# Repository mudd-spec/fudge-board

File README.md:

# fudge board
------ 
## Important!
This board charges batteries but does NOT run off batteries connected to the BAT and GND terminals. I plan to make a revised version where this is changed.

This is an RP2040 dev board created based off the <a href="https://github.com/KaiPereira/build-a-devboard">guide</a> from Blueprint at Hackclub!

### Features
- RP2040 Chip
- 12MHz Crystal Oscillator
- Many GPIO Pins
- a 1 Cell Lipo/Li-ion Battery Charger
- LED connected to GPIO
- USB-C
- 16MB of Flash Memory
- LDO Power Regulator

#### KiCad
The entire board was made with this software! The pictures below are taken from KiCad!

<strong>Schematic</strong>

<strong>PCB</strong>

#### JLCPCB
Here is a sample of what manufacturing the board might cost.

<strong>BOM</strong>

<strong>Final Price</strong>

#### Excalidraw
All silkscreen drawings were made with this handy website.
#### Extra
From this project I learned a lot more about how common communication interfaces like SPI, UART, and I2C work. I quickly picked up on electronics basics such as the theory behind decoupling capacitors, pull-up/pull-down resistors, and common electronics components (flash memory ics, crystal oscillators, etc.). I hope with this knowledge, I can continue on to put together a little single board computer, like the common Raspberry Pi.

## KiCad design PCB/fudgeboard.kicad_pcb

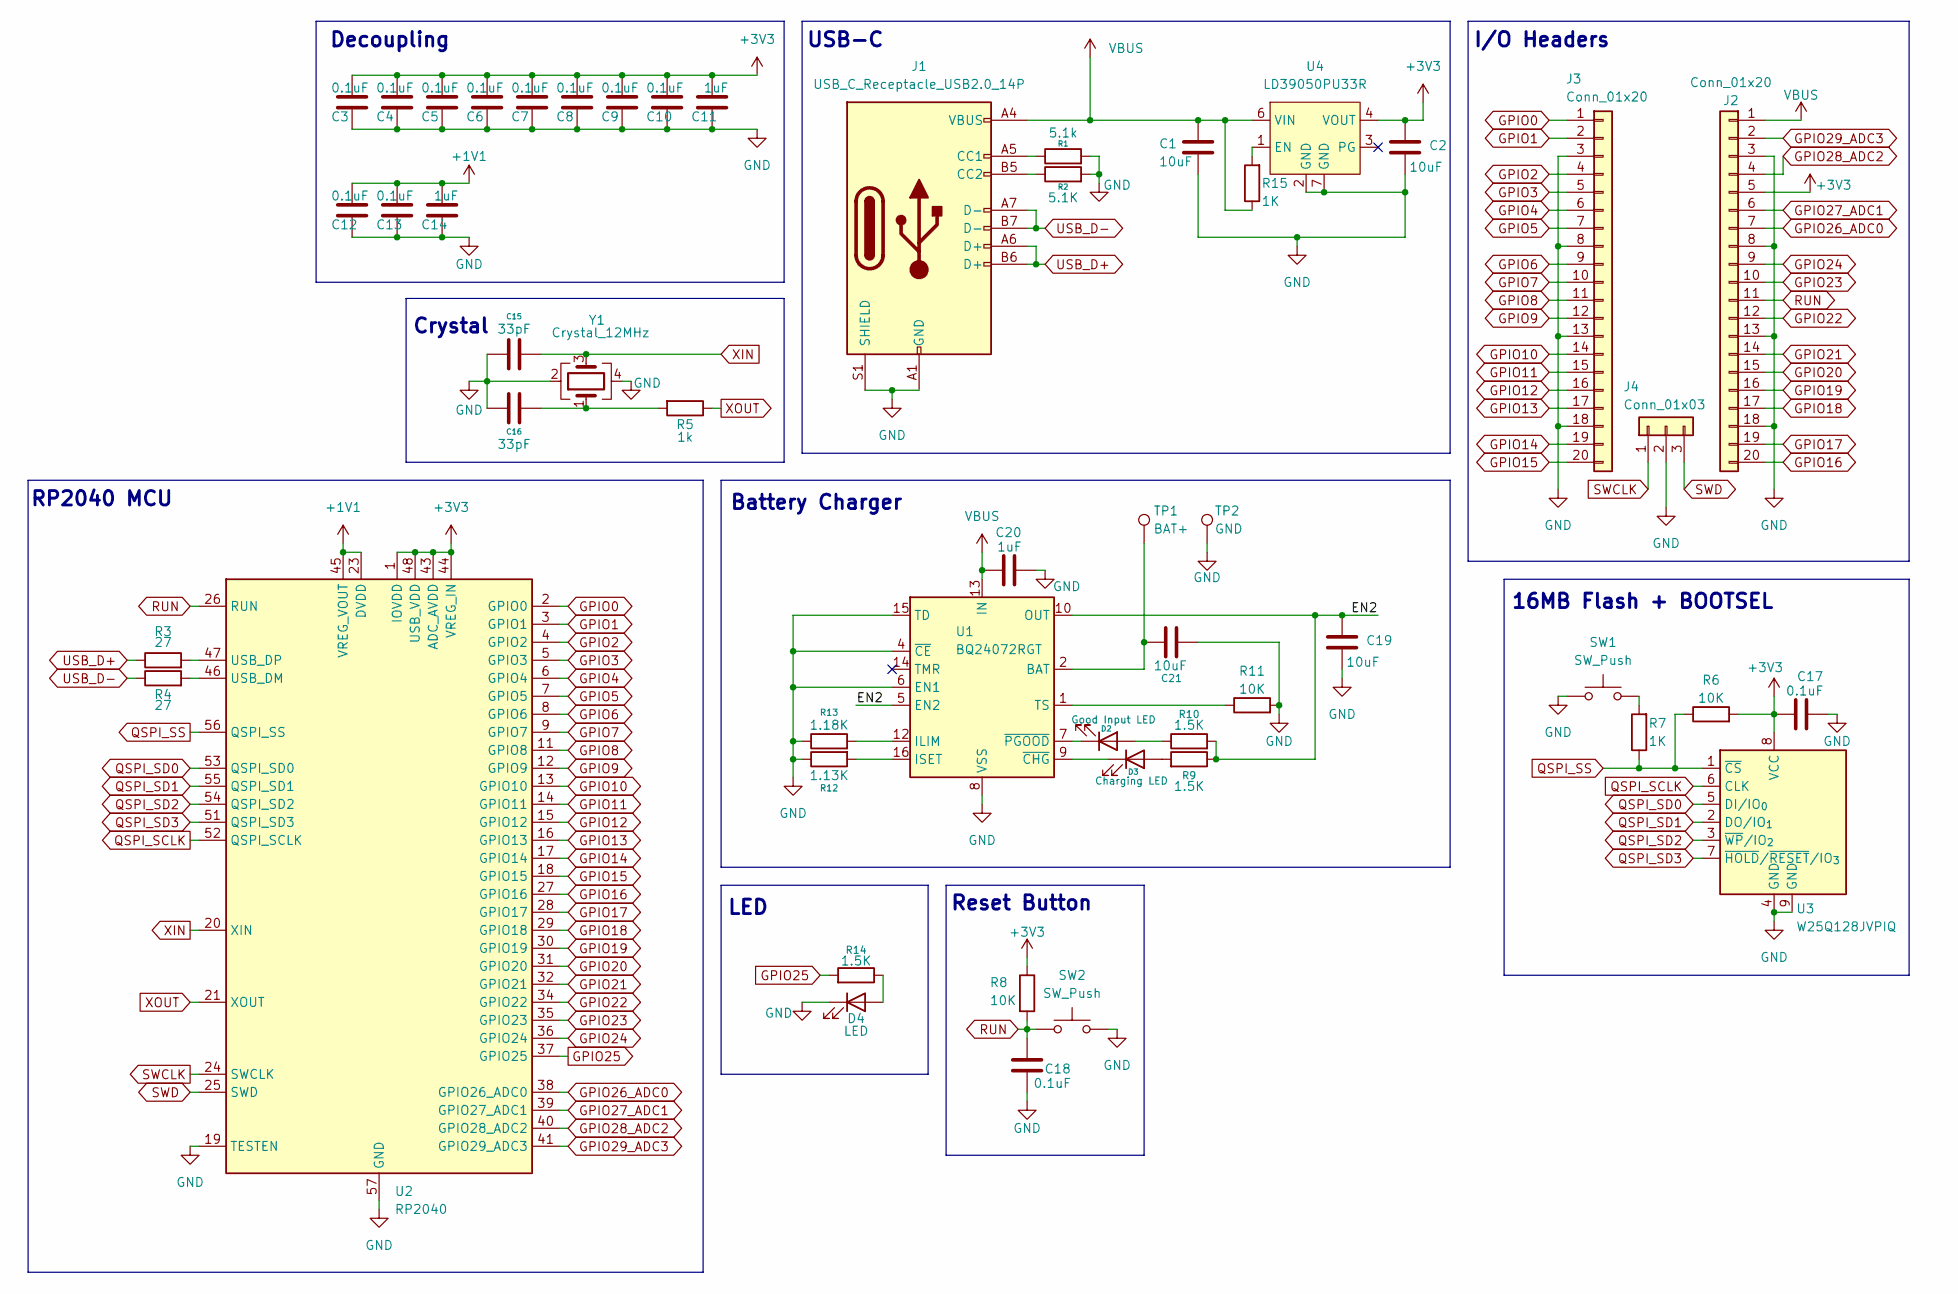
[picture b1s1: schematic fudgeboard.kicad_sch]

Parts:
C1, C2, C19, C21: 10uF; C_0603_1608Metric
C3, C4, C5, C6, C7, C8, C9, C10, C12, C13, C17, C18: 0.1uF; C_0402_1005Metric
C11, C14, C20: 1uF; C_0402_1005Metric
C15, C16: 33pF; C_0402_1005Metric
D2: Good Input LED; LED_0603_1608Metric
D3: Charging LED; LED_0603_1608Metric
D4: LED; LED_0603_1608Metric
J1: USB_C_Receptacle_USB2.0_14P; USB_C_Receptacle_HRO_TYPE-C-31-M-12
J2, J3: Conn_01x20; PinHeader_1x20_P2.54mm_Vertical
J4: Conn_01x03; PinHeader_1x03_P2.54mm_Vertical
R1: 5.1k; R_0402_1005Metric
R2: 5.1K; R_0402_1005Metric
R3, R4: 27; R_0402_1005Metric
R5: 1k; R_0402_1005Metric
R6, R8, R11: 10K; R_0402_1005Metric
R7, R15: 1K; R_0402_1005Metric
R9, R10, R14: 1.5K; R_0402_1005Metric
R12: 1.13K; R_0402_1005Metric
R13: 1.18K; R_0402_1005Metric
SW1, SW2: SW_Push; SW_Push_SPST_NO_Alps_SKRK
TP1: BAT+; TestPoint_Pad_2.5x2.5mm
TP2: GND; TestPoint_Pad_2.5x2.5mm
U1: BQ24072RGT; VQFN-16-1EP_3x3mm_P0.5mm_EP1.6x1.6mm
U2: RP2040; QFN-56-1EP_7x7mm_P0.4mm_EP3.2x3.2mm
U3: W25Q128JVPIQ; WSON-8-1EP_6x5mm_P1.27mm_EP3.4x4mm
U4: LD39050PU33R; DFN-6-1EP_3x3mm_P0.95mm_EP1.7x2.6mm
Y1: Crystal_12MHz; Crystal_SMD_3225-4Pin_3.2x2.5mm

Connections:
+1V1: C12.1, C13.1, C14.1, U2.23 (DVDD), U2.45 (VREG_VOUT), U2.50 (DVDD)
+3V3: C2.1, C3.1, C4.1, C5.1, C6.1, C7.1, C8.1, C9.1, C10.1, C11.1, C17.1, J2.5, R6.2, R8.1, U2.1 (IOVDD), U2.10 (IOVDD), U2.22 (IOVDD), U2.33 (IOVDD), U2.42 (IOVDD), U2.43 (ADC_AVDD), U2.44 (VREG_IN), U2.48 (USB_VDD), U2.49 (IOVDD), U3.8 (VCC), U4.4 (VOUT)
/EN2: C19.1, R9.1, R10.2, U1.5 (EN2), U1.10 (OUT), U1.11 (OUT)
GND: C1.2, C2.2, C3.2, C4.2, C5.2, C6.2, C7.2, C8.2, C9.2, C10.2, C11.2, C12.2, C13.2, C14.2, C15.1, C16.1, C17.2, C18.2, C19.2, C20.1, C21.1, D4.1 (K), J1.A1 (GND), J1.A12 (GND), J1.B1 (GND), J1.B12 (GND), J1.S1 (SHIELD), J2.3, J2.8, J2.13, J2.18, J3.3, J3.8, J3.13, J3.18, J4.2, R1.2, R2.2, R11.2, R12.1, R13.1, SW1.1, SW2.2, TP2.1, U1.4 (~CE), U1.6 (EN1), U1.8 (VSS), U1.15 (TD), U1.17 (VSS), U2.19 (TESTEN), U2.57 (GND), U3.4 (GND), U3.9 (GND), U4.2 (GND), U4.7 (GND), Y1.2, Y1.4
GPIO0: J3.1, U2.2 (GPIO0)
GPIO1: J3.2, U2.3 (GPIO1)
GPIO2: J3.4, U2.4 (GPIO2)
GPIO3: J3.5, U2.5 (GPIO3)
GPIO4: J3.6, U2.6 (GPIO4)
GPIO5: J3.7, U2.7 (GPIO5)
GPIO6: J3.9, U2.8 (GPIO6)
GPIO7: J3.10, U2.9 (GPIO7)
GPIO8: J3.11, U2.11 (GPIO8)
GPIO9: J3.12, U2.12 (GPIO9)
GPIO10: J3.14, U2.13 (GPIO10)
GPIO11: J3.15, U2.14 (GPIO11)
GPIO12: J3.16, U2.15 (GPIO12)
GPIO13: J3.17, U2.16 (GPIO13)
GPIO14: J3.19, U2.17 (GPIO14)
GPIO15: J3.20, U2.18 (GPIO15)
GPIO16: J2.20, U2.27 (GPIO16)
GPIO17: J2.19, U2.28 (GPIO17)
GPIO18: J2.17, U2.29 (GPIO18)
GPIO19: J2.16, U2.30 (GPIO19)
GPIO20: J2.15, U2.31 (GPIO20)
GPIO21: J2.14, U2.32 (GPIO21)
GPIO22: J2.12, U2.34 (GPIO22)
GPIO23: J2.10, U2.35 (GPIO23)
GPIO24: J2.9, U2.36 (GPIO24)
GPIO25: R14.2, U2.37 (GPIO25)
GPIO26_ADC0: J2.7, U2.38 (GPIO26_ADC0)
GPIO27_ADC1: J2.6, U2.39 (GPIO27_ADC1)
GPIO28_ADC2: J2.4, U2.40 (GPIO28_ADC2)
GPIO29_ADC3: J2.2, U2.41 (GPIO29_ADC3)
unnamed: C16.2, R5.2, Y1.1
unnamed: C21.2, TP1.1, U1.2 (BAT), U1.3 (BAT)
unnamed: D2.2 (A), R10.1
unnamed: D2.1 (K), U1.7 (~PGOOD)
unnamed: D3.2 (A), R9.2
unnamed: D3.1 (K), U1.9 (~CHG)
unnamed: D4.2 (A), R14.1
unnamed: J1.A5 (CC1), R1.1
unnamed: J1.B5 (CC2), R2.1
unnamed: R7.2, SW1.2
unnamed: R13.2, U1.12 (ILIM)
unnamed: R12.2, U1.16 (ISET)
unnamed: R11.1, U1.1 (TS)
unnamed: R4.2, U2.46 (USB_DM)
unnamed: R3.2, U2.47 (USB_DP)
unnamed: R15.2, U4.1 (EN)
QSPI_SCLK: U2.52 (QSPI_SCLK), U3.6 (CLK)
QSPI_SD0: U2.53 (QSPI_SD0), U3.5 (DI/IO_{0})
QSPI_SD1: U2.55 (QSPI_SD1), U3.2 (DO/IO_{1})
QSPI_SD2: U2.54 (QSPI_SD2), U3.3 (~WP/IO_{2})
QSPI_SD3: U2.51 (QSPI_SD3), U3.7 (~HOLD/~RESET/IO_{3})
QSPI_SS: R6.1, R7.1, U2.56 (QSPI_SS), U3.1 (~CS)
RUN: C18.1, J2.11, R8.2, SW2.1, U2.26 (RUN)
SWCLK: J4.1, U2.24 (SWCLK)
SWD: J4.3, U2.25 (SWD)
USB_D+: J1.A6 (D+), J1.B6 (D+), R3.1
USB_D-: J1.A7 (D-), J1.B7 (D-), R4.1
VBUS: C1.1, C20.2, J1.A4 (VBUS), J1.A9 (VBUS), J1.B4 (VBUS), J1.B9 (VBUS), J2.1, R15.1, U1.13 (IN), U4.6 (VIN)
XIN: C15.2, U2.20 (XIN), Y1.3
XOUT: R5.1, U2.21 (XOUT)

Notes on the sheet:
Crystal
RP2040 MCU
I/O Headers
Reset Button
Decoupling
USB-C
16MB Flash + BOOTSEL
LED
Battery Charger

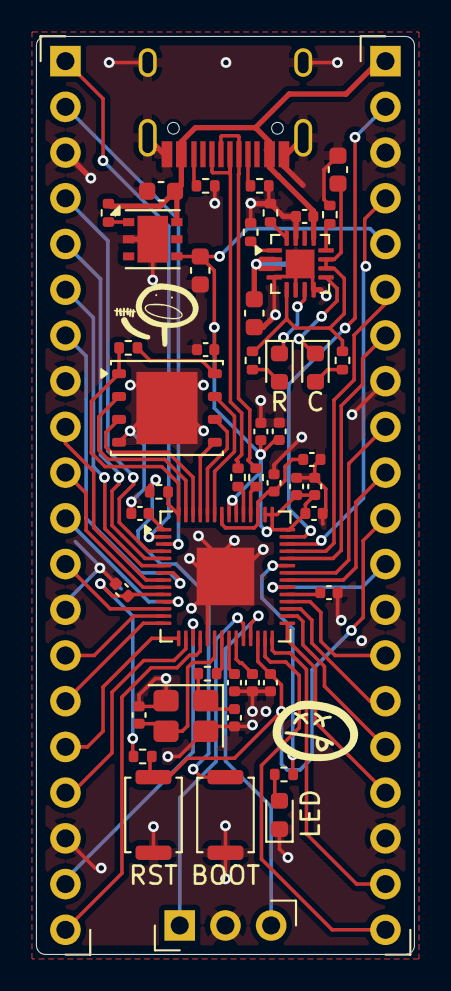
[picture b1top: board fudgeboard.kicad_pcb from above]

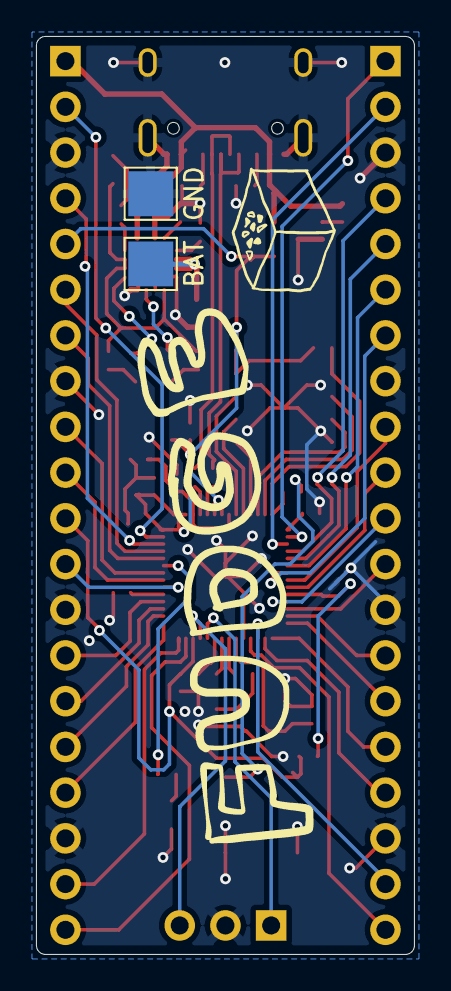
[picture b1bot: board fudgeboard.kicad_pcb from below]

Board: 2 copper layers, 21.0 x 51.0 mm, 52 parts (2 on the bottom side), 64 nets.

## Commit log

2025-12-31 add files
2025-12-31 add readme, round pcb edges, add images, fix bom csv and cpl csv
2025-12-31 test image zoom
